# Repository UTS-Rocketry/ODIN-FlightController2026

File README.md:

# ODIN - UTS Rocketry – Flight Controller 2026

## Version 1.0
Primary avionics flight controller for the 2026 AURC rocket.

This board manages flight state detection, sensor fusion, telemetry transmission, and onboard data logging using a 3.3V STM32-based embedded system.

---

## System Overview

### Microcontroller
- STM32 (F4 Series)
- 3.3V logic domain
- SWD debugging (ST-Link)
- Optional USB device (CDC / DFU)
- DMA-enabled peripherals
- Hardware timers for deterministic event timing

---

## Sensors

### Barometer (I2C)
- High-resolution pressure sensor
- Used for altitude estimation
- Data-ready interrupt supported (optional)
- VDD and VDDIO tied to 3.3V
- Local decoupling per datasheet

### IMU (Accelerometer + Gyroscope)
- Used for:
  - Boost detection
  - Apogee validation
  - Orientation monitoring
- Connected via SPI or I2C
- Interrupt-capable EXTI lines available

### GPS (UART)
- Real-time position tracking
- Logged to SD card
- Transmitted via LoRa telemetry
- Used for post-flight recovery

---

## Telemetry – SX1262 (SPI)

- LoRa-based long-range telemetry
- Configurable TX power & spreading factor
- SPI with DMA support
- Downlinked data:
  - Altitude
  - Velocity estimate
  - Flight state
  - GPS coordinates
  - Battery voltage

---

## Data Logging – microSD (SPI Mode)

- SPI selected over SDIO for routing simplicity and robustness
- 22Ω series resistor on SCK
- 10k pull-up on CS (DAT3)
- 0.1µF + 10µF local decoupling
- ESD protection on the connector

### Logged Parameters
- Timestamp
- Raw pressure
- Calculated altitude
- IMU acceleration & gyro
- GPS coordinates
- Flight state transitions
- Battery voltage
- Event flags

---

## Power Architecture

- Main system input rail
- 3.3V regulated logic rail
- ADC-based battery voltage monitoring (resistor divider)
- Local decoupling at each IC
- Bulk capacitance near SD and LoRa module

### Design Considerations
- All digital logic operates at 3.3V
- Short SPI traces with source termination
- Separation from switching regulator noise
- Solid ground reference plane

---

##  Programming & Debugging

### SWD (Primary Interface)
- SWDIO
- SWCLK
- GND
- 3.3V reference
- NRST (optional)

Used for:
- Firmware flashing
- Breakpoint debugging
- Register inspection

### USB (Optional)
- CDC virtual COM port for debug output
- Optional DFU firmware update support

---

### Core Features
- Sensor initialisation & health checks
- DMA-based peripheral handling
- Deterministic flight-state transitions
- SD logging with fault handling
- Telemetry packet scheduling
- Brownout and fault detection

---

# Contributors
 - Ollie Charleton: Avionics Lead
 - Michael Basangan: Software Lead
 - Aditya Sriram : Advisor

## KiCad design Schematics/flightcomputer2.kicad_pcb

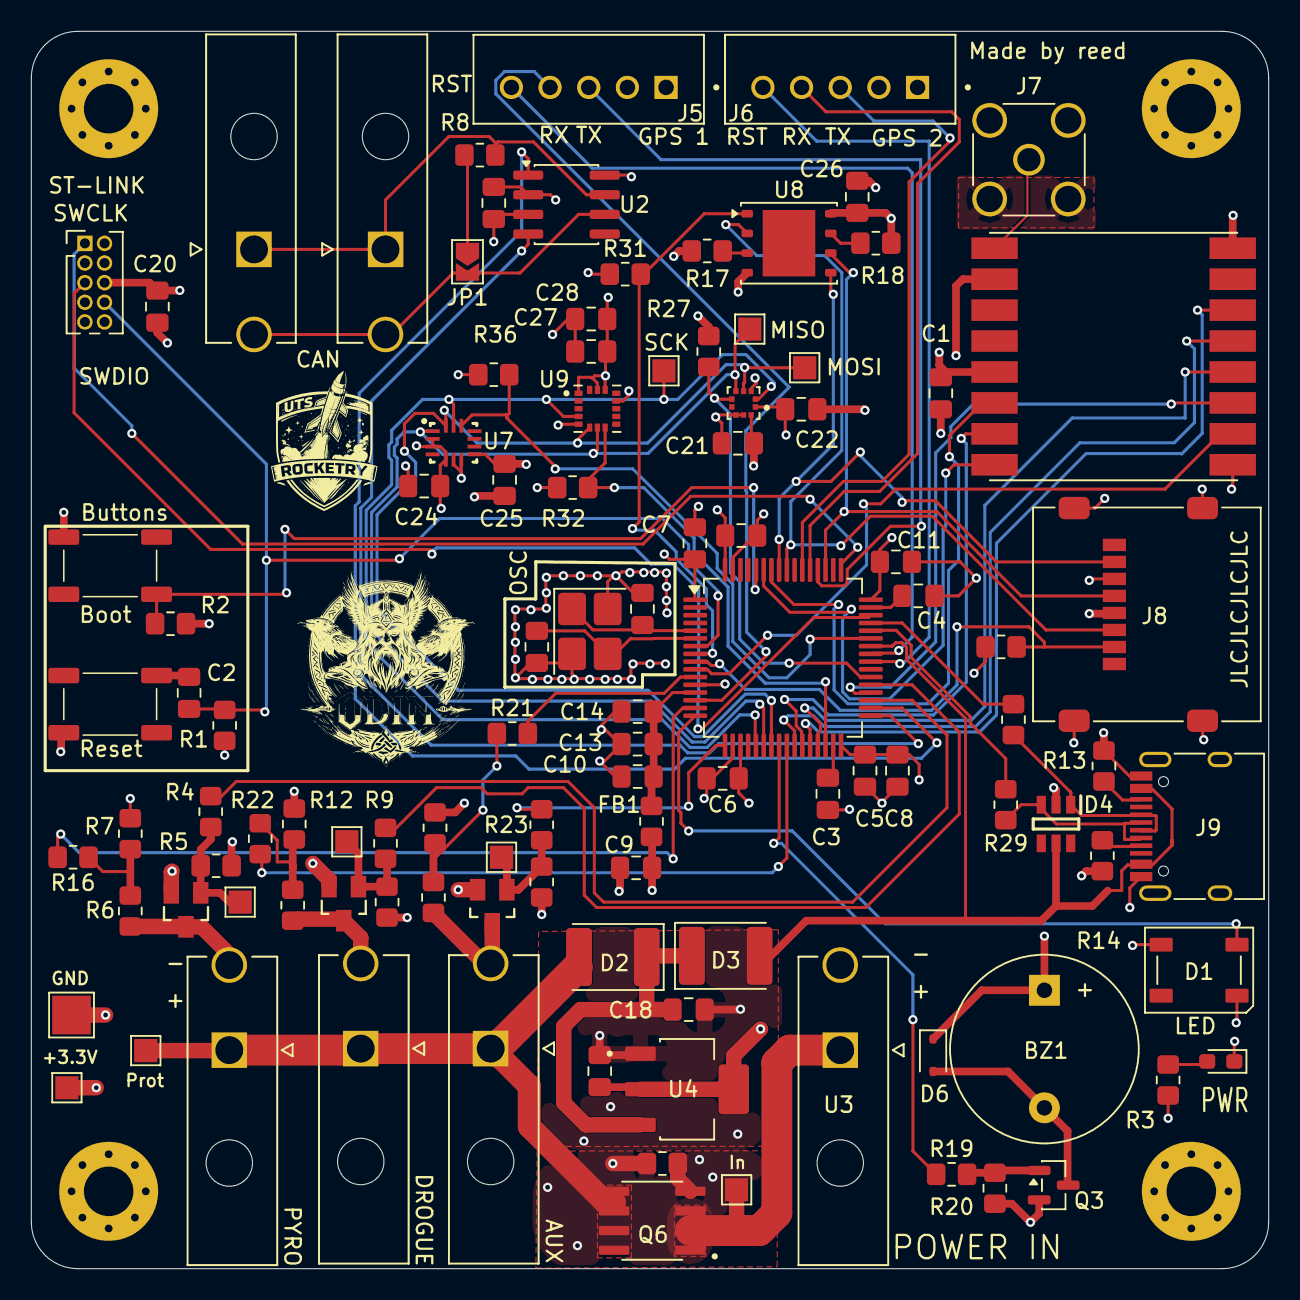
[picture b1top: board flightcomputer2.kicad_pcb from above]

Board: 4 copper layers, 80.0 x 80.0 mm, 107 parts (0 on the bottom side), 76 nets.

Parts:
BZ1: Buzzer; Buzzer_12x9.5RM7.6
C1, C2, C5, C6, C7, C10, C11, C12, C14, C17, C18, C20, C21, C22, C24, C25, C26, C27: 100nf; C_0805_2012Metric_Pad1.18x1.45mm_HandSolder
C3, C4: 2.2u; C_0805_2012Metric_Pad1.18x1.45mm_HandSolder
C8: 4.7u; C_0805_2012Metric_Pad1.18x1.45mm_HandSolder
C9, C13, C28: 1u; C_0805_2012Metric_Pad1.18x1.45mm_HandSolder
C15, C16: 18p; C_0805_2012Metric_Pad1.18x1.45mm_HandSolder
C19: 10u; C_0805_2012Metric_Pad1.18x1.45mm_HandSolder
CAN_IN1: CAN; MOLEX_26013114
CAN_OUT1: CAN; MOLEX_26013114
D1: ws2812b; LED_WS2812B_PLCC4_5.0x5.0mm_P3.2mm
D2, D3: D_Schottky; D_2114_3652Metric
D4: SRV05-4.TCT; SOT95P280X145-6N
D6: 1N5819WS; D_SOD-323
FB1: FerriteBead; R_0805_2012Metric_Pad1.20x1.40mm_HandSolder
J1: Microsemi_FlashPro-JTAG-10; PinHeader_2x05_P1.27mm_Vertical
J2, J10: Pyro; MOLEX_26013114
J4: Drouge; MOLEX_26013114
J5, J6: Conn_01x05_Pin; JST_B5B-XH-A
J7: Conn_Coaxial_Small; SMA_Amphenol_132291_Vertical
J8: Micro_SD_Card; microSD_HC_Molex_47219-2001
J9: USB_C_Receptacle_USB2.0_16P; USB_C_Receptacle_HRO_TYPE-C-31-M-12
JP1: SolderJumper_2_Open; SolderJumper-2_P1.3mm_Open_TrianglePad1.0x1.5mm
PowerLED1: RLED; LED_0603_1608Metric_Pad1.05x0.95mm_HandSolder
Q1, Q2, Q4: IRLML2502TRPBF; SOT23
Q3: BC817; SOT-23
Q6: Q_PMOS_GSD; SOIC127P599X175-8N
R1, R2, R5, R10, R15, R17, R18, R20, R24, R27, R31, R32, R36: 10k; R_0805_2012Metric_Pad1.20x1.40mm_HandSolder
R3, R16, R21, R22: 1k; R_0805_2012Metric_Pad1.20x1.40mm_HandSolder
R4, R9, R23: 100R; R_0805_2012Metric_Pad1.20x1.40mm_HandSolder
R6, R11, R25: 75k; R_0805_2012Metric_Pad1.20x1.40mm_HandSolder
R7, R12, R26, R30: 47k; R_0805_2012Metric_Pad1.20x1.40mm_HandSolder
R8: 120R; R_0805_2012Metric_Pad1.20x1.40mm_HandSolder
R13, R14: 5.1k; R_0805_2012Metric_Pad1.20x1.40mm_HandSolder
R19: 470r; R_0805_2012Metric_Pad1.20x1.40mm_HandSolder
R28, R29: 27r; R_0805_2012Metric_Pad1.20x1.40mm_HandSolder
SW1, SW2: SAMZO G4R0015010
TP1, TP2, TP3, TP5, TP6, TP7, TP8, TP9, TP10: TestPoint; TestPoint_Pad_1.5x1.5mm
TP4: TestPoint; TestPoint_Pad_2.5x2.5mm
U1: STM32F405RGT6; LQFP-64_10x10mm_P0.5mm
U2: SN65HVD230; SOIC-8_3.9x4.9mm_P1.27mm
U3: PowerIn; MOLEX_26013114
U4: LDL1117-3.3; SOT230P700X180-4N
U5: RFM95W-915S2; XCVR_RFM95W-915S2
U6: Bosch BMP388; PQFN50P200X200X80-10N
U7: LSM6DS3TR-C; LGA-14-2.5X3MM
U8: W25Q128JVP; WSON-8-1EP_6x5mm_P1.27mm_EP3.4x4.3mm
U9: H3LIS331DL; PQFN50P300X300X100-16N
Y1: 8mhz; Crystal_SMD_3225-4Pin_3.2x2.5mm_HandSoldering

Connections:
+3.3V: BZ1.1 (+), C1.1, C5.1, C6.1, C7.1, C8.1, C9.2, C11.1, C12.1, C17.1, C19.1, C20.1, C21.1, C22.1, C24.1, C25.1, C26.1, C27.2, C28.2, D1.1 (VDD), D6.1 (K), FB1.1, J1.6 (VJTAG), J5.1, J6.1, J8.4 (VDD), R1.1, R3.2, R15.1, R17.2, R18.2, R27.2, R31.1, R32.1, R36.1, SW2.1, TP3.1 (1_1), U1.1 (VBAT), U1.19 (VDD), U1.32 (VDD), U1.48 (VDD), U1.64 (VDD), U2.3 (VCC), U4.2 (Vout), U4.4 (Vout), U5.13 (3.3V), U6.1 (VDDIO), U6.10 (VDD), U7.2 (SDx), U7.3 (SCx), U7.5 (VDDIO), U7.8 (VDD), U8.8 (VCC), U9.1 (Vdd_IO), U9.14 (VDD), U9.15 (VDD)
+3.3VA: C10.2, C13.1, C14.1, FB1.2, U1.13 (VDDA)
+5V: D3.2 (A), D4.5, J9.A4 (VBUS), J9.A9 (VBUS), J9.B4 (VBUS), J9.B9 (VBUS), U1.42 (PA9)
+BATT: Q6.1 (S), Q6.2 (Source), Q6.3 (Source), TP1.1 (1_1), U3.1
/Accelerometer/Accelerometer_MIS0: TP8.1 (1_1), U1.22 (PA6), U6.5 (SDO), U7.1 (SDO/SA0), U9.7 (SDO/SA0)
/Accelerometer/Accelerometer_MOSI: TP9.1 (1_1), U1.23 (PA7), U6.4 (SDI), U7.14 (SDA), U9.6 (SDA/SDI/SDO)
/Accelerometer/Accelerometer_SPICLK: TP10.1 (1_1), U1.21 (PA5), U6.2 (SCK), U7.13 (SCL), U9.4 (SCL/SPC)
/Accelerometer/ChipslectAccelerometer: R32.2, U1.30 (PB11), U9.8 (CS)
/Aux/AuxADC: R21.2, U1.11 (PC3)
/Aux/AuxIgnite: R23.2, U1.17 (PA3)
/Aux/IgnitionPower: D2.2 (A), J2.1, J4.1, J10.1, Q6.5 (D), Q6.6 (Drain), Q6.7 (Drain), TP2.1 (1_1)
/Barometer/Baraometer-ChipSelect: R27.1, U1.38 (PC7), U6.6 (CS)
/Can_transceiver/CANH: CAN_IN1.1, CAN_OUT1.1, R8.1, U2.7 (CANH)
/Can_transceiver/CANL: CAN_IN1.2, CAN_OUT1.2, JP1.2 (B), U2.6 (CANL)
/Can_transceiver/CAN_RX_2: U1.33 (PB12), U2.4 (R)
/Can_transceiver/CAN_TX_2: U1.34 (PB13), U2.1 (D)
/Drogue/DrougeADC: R22.2, U1.25 (PC5)
/Drogue/DrougeIgnite: R9.2, U1.37 (PC6)
/FlashMemory/ChipSelectFLash: R31.2, U1.8 (PC0), U8.1 (~CS)
/FlashMemory/SPICLK: J8.5 (CLK), U1.51 (PC10), U8.6 (CLK)
/FlashMemory/SPI_MISO: J8.3 (CMD), U1.56 (PB4), U8.2 (DO/IO_{1})
/FlashMemory/SPI_MOSI: J8.7 (DAT0), U1.57 (PB5), U8.5 (DI/IO_{0})
/FlashSd/ChipSelectSDCARD: J8.2 (DAT3/CD), R15.2, U1.9 (PC1)
/GPS/GPS1_RX: J5.4, U1.14 (PA0)
/GPS/GPS1_TX: J5.3, U1.52 (PC11)
/GPS/GPS2_RX: J6.4, U1.53 (PC12)
/GPS/GPS2_TX: J6.3, U1.54 (PD2)
/GPS/RESET1: J5.5, U1.41 (PA8)
/GPS/RESET2: J6.5, U1.40 (PC9)
/IMU/ChipSelectIMU: R36.2, U1.43 (PA10), U7.12 (CS)
/LoRa/sxDIO0: U1.58 (PB6), U5.14 (DIO0)
/LoRa/sxDIO1: U1.27 (PB1), U5.15 (DIO1)
/LoRa/sxDIO2: U1.59 (PB7), U5.16 (DIO2)
/LoRa/sxMIS0: U1.10 (PC2), U5.2 (MISO)
/LoRa/sxMOSI: U1.36 (PB15), U5.3 (MOSI)
/LoRa/sxNSS: U1.26 (PB0), U5.5 (NSS)
/LoRa/sxReset: U1.28 (PB2), U5.6 (RESET)
/LoRa/sxSCK: U1.29 (PB10), U5.4 (SCK)
/MCU/BOOT0: R2.2, SW2.4, U1.60 (BOOT0)
/MCU/BuzzerControl: R19.1, U1.24 (PC4)
/MCU/D+: R28.2, U1.45 (PA12)
/MCU/D-: R29.2, U1.44 (PA11)
/MCU/NRST: C2.1, J1.8 (~TRST), R1.2, U1.7 (NRST)
/MCU/OSC IN: C15.1, U1.5 (PH0), Y1.1
/MCU/OSC OUT: C16.1, U1.6 (PH1), Y1.3
/MCU/PyroADC: R16.2, U1.15 (PA1)
/MCU/PyroIgnite: R4.2, U1.35 (PB14)
/MCU/RGB_DATA: D1.4 (DIN), U1.16 (PA2)
/MCU/SWCLK: J1.1 (TCK), U1.49 (PA14)
/MCU/SWDIO: J1.5 (TMS), U1.46 (PA13)
/usb_type_c/D+: D4.1, J9.A6 (D+), J9.B6 (D+), R28.1
/usb_type_c/D-: D4.3, J9.A7 (D-), J9.B7 (D-), R29.1
GND: C1.2, C3.2, C4.2, C5.2, C6.2, C7.2, C8.2, C9.1, C10.1, C11.2, C12.2, C13.2, C14.2, C15.2, C16.2, C17.2, C18.2, C19.2, C20.2, C21.2, C22.2, C24.2, C25.2, C26.2, C27.1, C28.1, D1.3 (VSS), D4.2, J1.2 (GND), J1.10 (GND), J5.2, J6.2, J7.2 (Ext), J8.6 (VSS), J8.9 (SHIELD), J9.A1 (GND), J9.A12 (GND), J9.B1 (GND), J9.B12 (GND), PowerLED1.1 (K), Q1.2 (S), Q2.2 (S), Q3.2 (E), Q4.2 (S), R2.1, R5.2, R7.2, R10.2, R12.2, R13.2, R14.2, R20.1, R24.2, R26.2, R30.2, SW1.3, TP4.1 (1_1), U1.12 (VSSA), U1.18 (VSS), U1.63 (VSS), U2.2 (GND), U2.8 (Rs), U3.2, U4.1 (GND), U5.1 (GND), U5.8 (GND), U5.10 (GND), U6.3 (VSS), U6.8 (VSS), U6.9 (VSS), U7.6 (GND), U7.7 (GND), U8.4 (GND), U9.5 (GND), U9.12 (GND), Y1.2, Y1.4
unnamed: BZ1.2 (-), D6.2 (A), Q3.3 (C)
unnamed: C2.2, SW1.2
unnamed: C18.1, D2.1 (K), D3.1 (K), U4.3 (Vin)
unnamed: J2.2, Q1.3 (D), R25.2
unnamed: J4.2, Q2.3 (D), R11.2
unnamed: J7.1 (In), U5.9 (ANT)
unnamed: J9.A5 (CC1), R14.1
unnamed: J9.B5 (CC2), R13.1
unnamed: J10.2, Q4.3 (D), R6.2
unnamed: JP1.1 (A), R8.2
unnamed: PowerLED1.2 (A), R3.1
unnamed: Q1.1 (G), R23.1, R24.1, TP6.1 (1_1)
unnamed: Q2.1 (G), R9.1, R10.1, TP7.1 (1_1)
unnamed: Q3.1 (B), R19.2, R20.2
unnamed: Q4.1 (G), R4.1, R5.1, TP5.1 (1_1)
unnamed: Q6.4 (G), R30.1
unnamed: R11.1, R12.1, R22.1
unnamed: R6.1, R7.1, R16.1
unnamed: R21.1, R25.1, R26.1
unnamed: C3.1, U1.31 (VCAP_1)
unnamed: C4.1, U1.47 (VCAP_2)
unnamed: R18.1, U8.7 (~HOLD/~RESET/IO_{3})
unnamed: R17.1, U8.3 (~WP/IO_{2})

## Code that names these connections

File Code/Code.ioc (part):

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Mcu.Name=STM32F405RGTx
Mcu.Package=LQFP64
Mcu.UserName=STM32F405RGTx
PA0-WKUP.Mode=Asynchronous
PA0-WKUP.Signal=UART4_TX
PA1.Signal=ADCx_IN1
PA10.GPIOParameters=PinState,GPIO_Label
PA10.GPIO_Label=CS_IMU
PA10.PinState=GPIO_PIN_SET
PA10.Signal=GPIO_Output
PA11.Mode=Device_Only
PA11.Signal=USB_OTG_FS_DM
PA12.Mode=Device_Only
PA12.Signal=USB_OTG_FS_DP
PA13.Mode=Serial_Wire
PA13.Signal=SYS_JTMS-SWDIO
PA14.Mode=Serial_Wire
PA14.Signal=SYS_JTCK-SWCLK
PA2.GPIOParameters=GPIO_Label
PA2.GPIO_Label=RGBLEDControl
PA2.Signal=S_TIM2_CH3
PA3.GPIOParameters=GPIO_Label
PA3.GPIO_Label=AuxIgnite
PA3.Signal=GPIO_Output
PA4.GPIOParameters=GPIO_Label
PA4.GPIO_Label=LoRaResetPin
PA4.Signal=GPIO_Output
PA5.Mode=Full_Duplex_Master
PA5.Signal=SPI1_SCK
PA6.Mode=Full_Duplex_Master
PA6.Signal=SPI1_MISO
PA7.Mode=Full_Duplex_Master
PA7.Signal=SPI1_MOSI
PA8.GPIOParameters=GPIO_Label
PA8.GPIO_Label=GPS1ResetPin
PA8.Signal=GPIO_Output
PA9.Mode=Activate_VBUS
PA9.Signal=USB_OTG_FS_VBUS
PB0.GPIOParameters=GPIO_Label
PB0.GPIO_Label=LoRaNssPin
PB0.Signal=GPIO_Output
PB1.Signal=GPIO_Input
PB10.Mode=Full_Duplex_Master
PB10.Signal=SPI2_SCK
PB11.GPIOParameters=PinState,GPIO_Label
PB11.GPIO_Label=CSAccelerometer
PB11.PinState=GPIO_PIN_SET
PB11.Signal=GPIO_Output
PB12.Mode=CAN_Activate
PB12.Signal=CAN2_RX
PB13.Mode=CAN_Activate
PB13.Signal=CAN2_TX
PB14.GPIOParameters=GPIO_Label
PB14.GPIO_Label=PyroIgnite
PB14.Signal=GPIO_Output
PB15.Mode=Full_Duplex_Master
PB15.Signal=SPI2_MOSI
PB3.Signal=SYS_JTDO-SWO
PB4.Mode=Full_Duplex_Master
PB4.Signal=SPI3_MISO
PB5.Mode=Full_Duplex_Master
PB5.Signal=SPI3_MOSI
PB6.GPIOParameters=GPIO_Label
PB6.GPIO_Label=LoRaDIO0
PB6.Signal=GPIO_Output
PB7.GPIOParameters=GPIO_Label
PB7.GPIO_Label=LoRaDIO2
PB7.Signal=GPIO_Output
PC0.GPIOParameters=PinState,GPIO_Label
PC0.GPIO_Label=CSFlashmMemory
PC0.PinState=GPIO_PIN_SET
PC0.Signal=GPIO_Output
PC1.GPIOParameters=PinState,GPIO_Label
PC1.GPIO_Label=CS_SD_Card
PC1.PinState=GPIO_PIN_SET
PC1.Signal=GPIO_Output
PC10.Mode=Full_Duplex_Master
PC10.Signal=SPI3_SCK
PC11.Mode=Asynchronous
PC11.Signal=UART4_RX
PC12.Mode=Asynchronous
PC12.Signal=UART5_TX
PC2.Mode=Full_Duplex_Master
PC2.Signal=SPI2_MISO
PC3.Signal=ADCx_IN13
PC4.GPIOParameters=GPIO_Label
PC4.GPIO_Label=BuzzerControl
PC4.Signal=GPIO_Output
PC5.Signal=ADCx_IN15
PC6.GPIOParameters=PinState,GPIO_Label
PC6.GPIO_Label=DrougeIgnite
PC6.PinState=GPIO_PIN_RESET
PC6.Signal=GPIO_Output
PC7.GPIOParameters=PinState,GPIO_Label
PC7.GPIO_Label=CSBarometer
PC7.PinState=GPIO_PIN_SET
PC7.Signal=GPIO_Output
PC9.GPIOParameters=GPIO_Label
PC9.GPIO_Label=GPS2ResetPin
PC9.Signal=GPIO_Output
PD2.Mode=Asynchronous
PD2.Signal=UART5_RX
PH0-OSC_IN.Mode=HSE-External-Oscillator
PH0-OSC_IN.Signal=RCC_OSC_IN
PH1-OSC_OUT.Mode=HSE-External-Oscillator
PH1-OSC_OUT.Signal=RCC_OSC_OUT
RCC.HSE_VALUE=8000000
RCC.SYSCLKFreq_VALUE=72000000
RCC.SYSCLKSource=RCC_SYSCLKSOURCE_PLLCLK
board=custom

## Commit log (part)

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2026-03-01 Schematic changes
2026-03-03 output files got quote
2026-03-04 finalized output files
2026-03-14 ran dmf check fixed some things
2026-03-16 dfm sent for ordering
2026-03-19 added DIO0 and DIO2 pins to read lora module outputs
2026-03-19 updated .gitignore and fixed rf impedance things
2026-03-31 completed first draft of BMP388 Barometric Driver will move on to next sensor
2026-04-01 wrote HAL for H3 just need to port it over for the LS
2026-04-02 began writing CAN header file with enums and structs for message protcol
2026-04-03 updated structs for can
2026-04-03 same edit just forgot to save please look a previous commit
2026-04-04 began writing lora drivers beginning with reg defines in the header file
2026-04-05 finished sx1276 defines and added documentation moving on to struct construction for lora init
2026-04-20 added SD card middle ware from cubemx
2026-04-21 changed several pin defs, added swo pin for debug and added pulldown to pb2 for boot modes
2026-04-21 changed clock source for higher speed
2026-04-23 fixed BMP388 commit
2026-04-28 validated sensors workingvia spi, on to uart output of the values
2026-04-28 fixed linker error where floats would not print over uart, validated the barometer gives altitude relative to ground pressure
2026-04-29 accel works, prints over uart
2026-04-30 wrote calibration for imu
2026-04-30 finished implementation for read now need to check via uart if it works
2026-04-30 compiled
2026-04-30 sensors bus is working
2026-04-30 buzzer test, need to fix led next
2026-05-03 Added Files for application layer, added flight state machine documentation, added custom symbol folder
2026-05-03 checker for barometer external read
2026-05-04 finished lora driver code now need to test
2026-05-04 refactored main to seperate functions to keep main clean
2026-05-04 refactor works on serial
